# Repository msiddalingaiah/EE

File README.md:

# EE
A collection of engineering resources

# License

MIT License

Copyright (c) 2025 Madhu Siddalingaiah

Permission is hereby granted, free of charge, to any person obtaining a copy
of this software and associated documentation files (the "Software"), to deal
in the Software without restriction, including without limitation the rights
to use, copy, modify, merge, publish, distribute, sublicense, and/or sell
copies of the Software, and to permit persons to whom the Software is
furnished to do so, subject to the following conditions:

The above copyright notice and this permission notice shall be included in all
copies or substantial portions of the Software.

THE SOFTWARE IS PROVIDED "AS IS", WITHOUT WARRANTY OF ANY KIND, EXPRESS OR
IMPLIED, INCLUDING BUT NOT LIMITED TO THE WARRANTIES OF MERCHANTABILITY,
FITNESS FOR A PARTICULAR PURPOSE AND NONINFRINGEMENT. IN NO EVENT SHALL THE
AUTHORS OR COPYRIGHT HOLDERS BE LIABLE FOR ANY CLAIM, DAMAGES OR OTHER
LIABILITY, WHETHER IN AN ACTION OF CONTRACT, TORT OR OTHERWISE, ARISING FROM,
OUT OF OR IN CONNECTION WITH THE SOFTWARE OR THE USE OR OTHER DEALINGS IN THE
SOFTWARE.

# Subprojects

Several FPGA board examples based on [IceStorm](https://clifford.at/icestorm) open source tools are included. For example:

* [ICEBlink40](https://www.latticesemi.com/iceblink40-hx1k)
* [AlchitryCu](https://www.sparkfun.com/products/16526)
* [Nandland Go Board](https://nandland.com/the-go-board/) 
* [iceFUN](https://www.robotshop.com/products/icefun-fpga-board) [schematic](https://cdn.robotshop.com/media/d/dev/rb-dev-99/pdf/icefun-fpga-board-schematic.pdf) [github](https://github.com/devantech/iceFUN)

## Github Personal Access Token

* Create fine grained [personal access token](https://docs.github.com/en/authentication/keeping-your-account-and-data-secure/managing-your-personal-access-tokens#creating-a-fine-grained-personal-access-token)
 * Select repos
 * Repository Permissions | Contents  | Read and write

```
$ cd $docs/github/EE
$ git remote set-url origin https://<USER>:<TOKEN>@github.com/<USER>/EE.git
```

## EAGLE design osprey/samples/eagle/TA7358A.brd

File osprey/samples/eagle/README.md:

# Eagle samples

Drop Eagle files here. Keep a matching `.sch` and `.brd` together under the same base name, e.g.:

```
blinky.sch
blinky.brd
mylib.lbr
```

Files must be Eagle 6+ (XML format). Older binary files need to be opened and re-saved in Eagle 6 or later first.

The app lists each `.sch` + `.brd` pair as a sample to import, each `.lbr` as a library to
browse (and add parts from), and each `.dru` as design rules to load for the DRC.
Pairs are also used by the tests; `TA7358A` has a native counterpart in `../osprey/`.
Each `.cam` (an Eagle CAM job) is offered in the CAM menu. `TA7358A_2026-06-12.zip` is Eagle's CAM output for
`TA7358A` with `jlcpcb_2_layer_v9.cam`; the tests compare Osprey's CAM output against it.

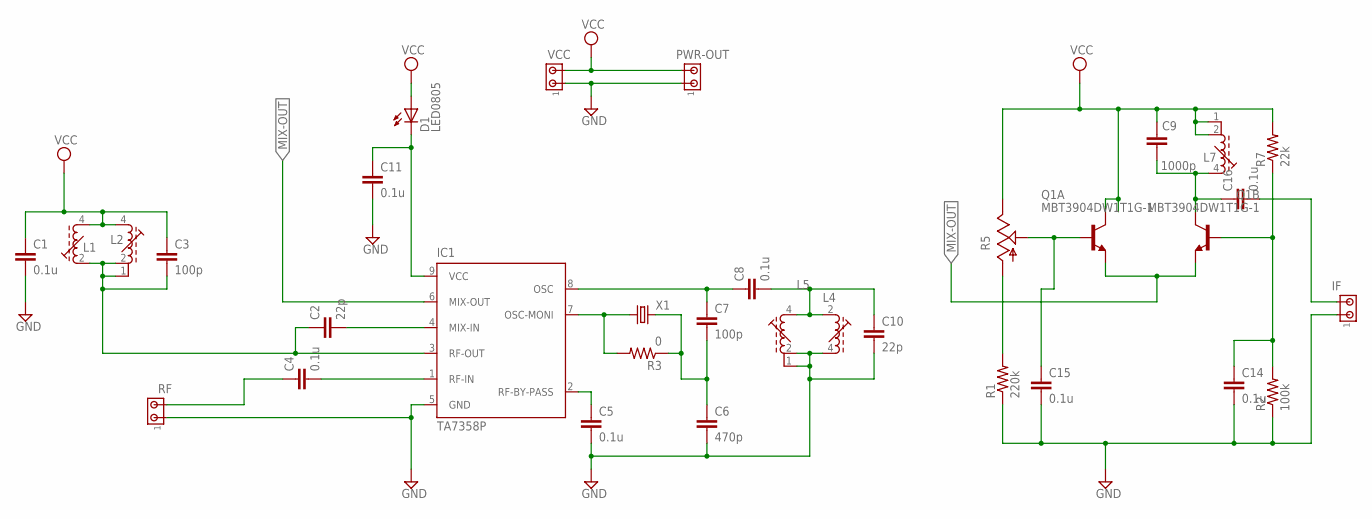
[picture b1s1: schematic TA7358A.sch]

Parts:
C1, C4, C5, C8, C11, C14, C15, C16: 0.1u; 0805
C2: 22p; 0805
C3, C7: 100p; CAP-0.2
C6: 470p; CAP-0.2
C9: 1000p; CAP-0.2
C10: 22p; CAP-0.2
D1: LED0805; 0805
IC1: TA7358P; SIP9-P-2.54A
IF: BERG-2
L1, L4: INDUCTOR-VAR-TOKO5K; TOKO5K
L2, L5, L7: INDUCTOR-VAR271K2; 71K2
PWR-OUT: BERG-2
Q1: MBT3904DW1T1G-1; SOT363
R1: 220k; 0805
R2: 100k; 0805
R3: 0; 0805
R5: 100k; RM-065
R7: 22k; 0805
RF: BERG-2
VCC: BERG-2
X1: CRYSTALHC49S; HC49/S

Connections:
GND: C1.2, C5.2, C6.2, C10.2, C11.2, C14.2, C15.2, IC1.5 (GND), IF.1, L4.4 (E), L5.1 (E1), L5.2 (E), PWR-OUT.1, R1.1, R2.1, RF.1, VCC.1
MIX-OUT: IC1.6 (MIX-OUT), Q1.1 (E), Q1.4 (E)
unnamed: C2.2, IC1.4 (MIX-IN)
unnamed: C4.2, IC1.1 (RF-IN)
unnamed: C2.1, C3.2, IC1.3 (RF-OUT), L1.2 (A), L2.1 (E1), L2.2 (E)
unnamed: C4.1, RF.2
unnamed: C5.1, IC1.2 (RF-BY-PASS)
unnamed: C16.2, IF.2
unnamed: C7.1, C8.1, IC1.8 (OSC)
unnamed: IC1.7 (OSC-MONI), R3.2, X1.1
unnamed: C6.1, C7.2, R3.1, X1.2
unnamed: C14.1, Q1.2 (B), R2.2, R7.1
unnamed: R1.2, R5.CCW
unnamed: C11.1, D1.1 (C), IC1.9 (VCC)
unnamed: C9.2, C16.1, L7.4 (A), Q1.6 (C)
unnamed: C15.1, Q1.5 (B), R5.CT
VCC: C1.1, C3.1, C9.1, D1.2 (A), L1.4 (E), L2.4 (A), L7.1 (E1), L7.2 (E), PWR-OUT.2, Q1.3 (C), R5.CW, R7.2, VCC.2
VCC1: C8.2, C10.1, L4.2 (A), L5.4 (A)

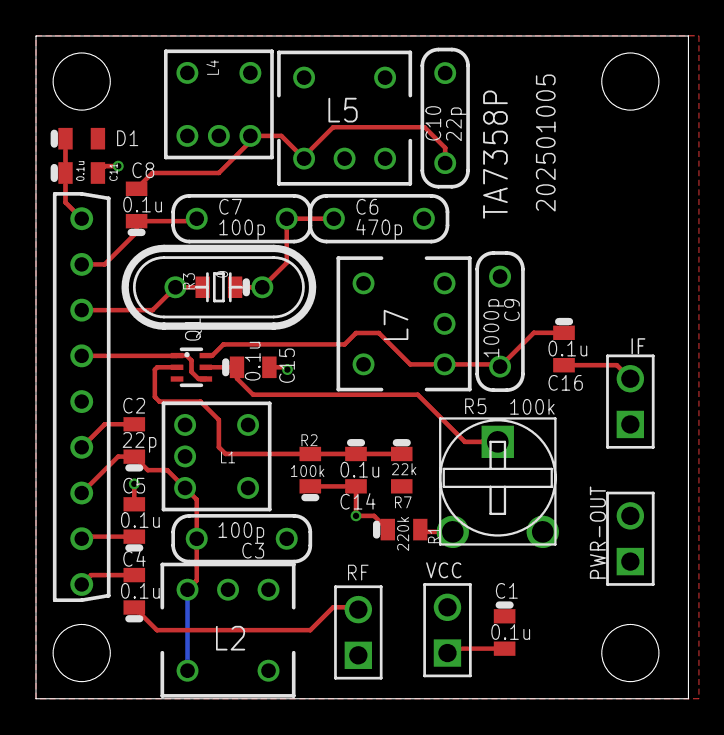
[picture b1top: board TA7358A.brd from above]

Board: 2 copper layers, 36.2 x 36.8 mm, 32 parts (0 on the bottom side), 18 nets.

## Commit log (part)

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2021-05-12 +Notebooks
2022-04-23 +HDLite initial rev
2022-04-23 test commit
2022-04-26 Improve Vector performance
2022-04-26 Functioning control panel
2022-04-26 Code clean up
2022-04-27 LED displays, refactor indicators
2022-04-27 +Bitslice control panel
2022-04-27 +CP internal signals, power on reset, window size
2022-04-27 +LabelFrame, UI improvements
2022-04-28 +Clock timer, start/stop/step/stepn
2022-04-28 +InputFrame, bug fixes, cleanup
2022-04-29 Refactor Vector
2022-04-29 Refactor Signal
2022-04-29 Improve IO, +Am2901, alu_test, input response
2022-04-29 +Nand, more signal refactoring, tests
2022-05-01 +alu_test display internal regs
2022-05-07 +Sigma logic equations
2022-05-07 Sigma fixes, CPU6 initial rev
2022-05-07 Slice fixes, sequencer fixes, VCD output
2022-05-08 Fix ALU bugs, confirm first loop
2022-05-09 Fix ALU write bug, add more signals for tracing
2022-05-13 Catch up with Verilog, instruction decode verified
2022-05-28 +iCEBlink40 icestorm examples
2022-05-28 Traffic light microcode assembler
2022-05-30 AlchitryCu blink 20MHz
2022-06-04 +pyAP
2022-06-04 pyAP basic code generation
2022-06-04 +traffic.ap
2022-06-04 +DParser, do1
2022-06-04 Refactor do1
2022-06-05 Refactor DParser
2022-06-05 Refactor, support com bitlist variable
2022-06-05 Improve do1
2022-06-06 Big AP refactor
2022-06-06 Superclass refactor
2022-06-06 Forward references and file write
2022-06-07 Refactor, CNAME needs work
2022-06-08 CNAME fix
2022-06-09 Refactor
2022-06-10 Bug fixes, do/else/fin support
2022-06-10 Add operators, fix uminus
2022-06-10 Multiple CNAMEs
2022-06-13 Char, hex support, bug fixes, cpu6 testing
2022-06-14 Error handling
2022-06-14 List support, strings almost working
2022-06-16 AP strings, cf/af fixes
2022-06-18 Refactor, line numbers
2022-06-18 BOUND directive
2022-06-24 Centurion updates, CPU6 almost there...
2022-06-25 Bug fixes, HDLite CPU6 almost executing
2022-08-21 +Sequencer/Parser
2022-08-22 +Sequencer, SequencerTB
2023-07-15 +NandlandGo example
2023-07-15 Old commits
2023-07-15 .gitignore
2023-07-15 +README
2023-07-15 +iceFUN blinky
2023-07-16 README
2023-07-31 Initial version
2023-07-31 +C file, big_endian.py
2023-08-01 +tb.v
2023-08-02 Memory read/write
2023-08-03 +CPU, PM, DM
2023-08-03 Basic instructions
2023-08-04 Fix pipeline fetch
2023-08-12 Fix lw/addi data hazard
2023-08-12 Doc updates
2023-08-12 +Op decode, ALU not wired yet
2023-08-12 WIre in ALU
2023-08-13 Simplify ALU input mux
2023-08-13 Replace constants with parameters
2023-08-13 Partial branch, needs condition check...
2023-08-13 Working BGE
2023-08-13 +Char output, LUI
2023-08-13 +Bubble lw/sw
2023-08-13 +JALR, needs testing
2023-08-14 Improve disassembly in Makefile
2023-08-14 JAL/JALR fix and test
2023-08-14 Refactor files
2023-08-16 Refactor pm/dm width
2023-08-17 +halt/sim_end
2023-08-17 +DM init
2023-08-18 Fix lw hazard, branch, +test
2023-08-19 Clock/instruction count
2023-08-19 More unit test
2023-08-19 Refactor, +decoder
2023-08-19 -Dead code
2023-08-22 +MCL65
2023-08-26 +M6502
2023-08-26 Refactor DecodeLogic, pc_inc, lda
2023-08-26 lda, nop, jmp operational
2023-08-26 ldx, ldy
2023-08-26 sta/lda abs
2023-08-27 Google sheet to decode logic
2023-08-27 Replace PC_INC with PC_HOLD, generated logic
2023-08-29 Basic ALU logic
2023-08-29 +ADC, uart print
2024-11-17 +Pong
2024-11-23 Pong refactor
2024-11-24 +VGA
2024-11-24 +VGA TestBench
2024-11-24 VGA bouncing ball
2024-11-24 VGA: refactor constants
2024-11-24 VGA: change colors
2024-11-25 +VGA working Pong
2024-11-25 VGA pong with LED score keeping
2024-11-25 Minor fixes, +README
2024-11-25 +README, png
2024-11-27 Quiet make, +usb.bat, README
2024-12-02 Sprites initial rev
2024-12-03 [VGA] Improve utilization with constant sizing
2024-12-03 [VGA] resource reduction
2024-12-03 [M6502] encode flags
2024-12-03 [Sprites] render selected sprites
2024-12-06 [Sprites] Refactor sprite memory
2024-12-07 Single sprite motion
2024-12-07 Line RAM almost working
2024-12-07 Working line RAM
2024-12-07 Minor refactor
2024-12-08 README design update
2024-12-08 README formatting
2024-12-08 CPU stack machine docs
2024-12-08 Functional playfield, needs alignment
2024-12-08 1kB playfield RAM
2024-12-10 +I8CPU
2024-12-11 Minimal compiler/code generation
2024-12-12 Initial CPU integration
2024-12-12 Async CPU write
2024-12-13 While loop
2024-12-14 +12-bit CPU, AND/OR/XOR/SL6
2024-12-15 Bug fixes, I/O access not fully functional
2024-12-15 Fix code load bug, minimal I/O works
2024-12-16 LED I/O support, code gen refactor
2024-12-16 Compiler AND/OR/XOR
2024-12-16 Functional I/O, vertical_int
2024-12-17 Fix reset bugs
2024-12-17 Support <, != operators
2024-12-17 +CPU controlled single motion sprite
2024-12-18 Refactor reset
2024-12-18 Fix big while loops
2024-12-18 +loop
2024-12-18 RAM read delay slot
2024-12-19 +if/else statement
2024-12-19 2-byte immediate, LT bug fix
2024-12-19 +AND/OR/XOR/Shift
2024-12-20 Switch input, SL bug fix
2024-12-20 Refactor code gen, stats summary
2024-12-21 Windows oss-cad-suite instructions
2024-12-21 Support >, iverilog 13 requires declarations before use
2024-12-21 Beginnings of lunar lander
2024-12-22 Shift ops, comments, fractional lunar lander, mem corruption?
2024-12-22 Lunar lander bug fix
2024-12-22 Refactor ioport, var
2024-12-22 Split Compiler/CodeGenerator
2024-12-22 Playfied sprite ROM, needs rendering alignment
2024-12-23 +Windows oss-cad-suite, icefunprog.py
2024-12-23 [iceFUN] StackMachine initial rev
2024-12-24 RAM address forwarding
2024-12-24 CPU RAM address forwarding
2024-12-25 Fix playfield sprite alignment
2024-12-25 Fix motion sprite rendering, 8 bit range
2024-12-25 Use constants
2024-12-25 Refactor, images
2024-12-25 README updates
2024-12-25 Resize images
2024-12-25 Improve game play
2024-12-25 16 bit CPU
2024-12-25 16-bit CPU
2024-12-25 Improve sprites and playfield
2024-12-27 Reduce 1 BRAM to 256 x 16 bit CPU RAM
2024-12-28 16 bit BRAM data stack, swap untested
2025-01-08 Pythonify embedded language
2025-01-09 +LineScanner
2025-01-09 Refactor read
2025-01-14 Refactor parseStatList
2025-03-02 +License
2025-03-25 +ATtiny412.ino
2025-03-25 +docs
2025-03-25 +image
2025-03-25 Resize image
2025-06-06 +ATtiny 412 Demod
2025-06-15 20kHz sample rate, MUXPOS bug fix
2025-08-31 +lc calculator
2025-09-14 I/Q sampling
2025-09-17 Faster isqrt
2025-09-17 Unsigned isqrt
2025-09-20 +alpha-beta min/max magnitude
2025-09-25 Create/move into directory
2025-09-25 +ESP32
2025-09-26 Magnitude timing
2025-12-13 Initial rev
2025-12-13 Address forwarding, README
2025-12-13 README fixes
2025-12-14 All instructions, synthesis, README
2025-12-14 README utilization
2025-12-14 README tools
2026-05-11 +SN76477 AVR sketch
